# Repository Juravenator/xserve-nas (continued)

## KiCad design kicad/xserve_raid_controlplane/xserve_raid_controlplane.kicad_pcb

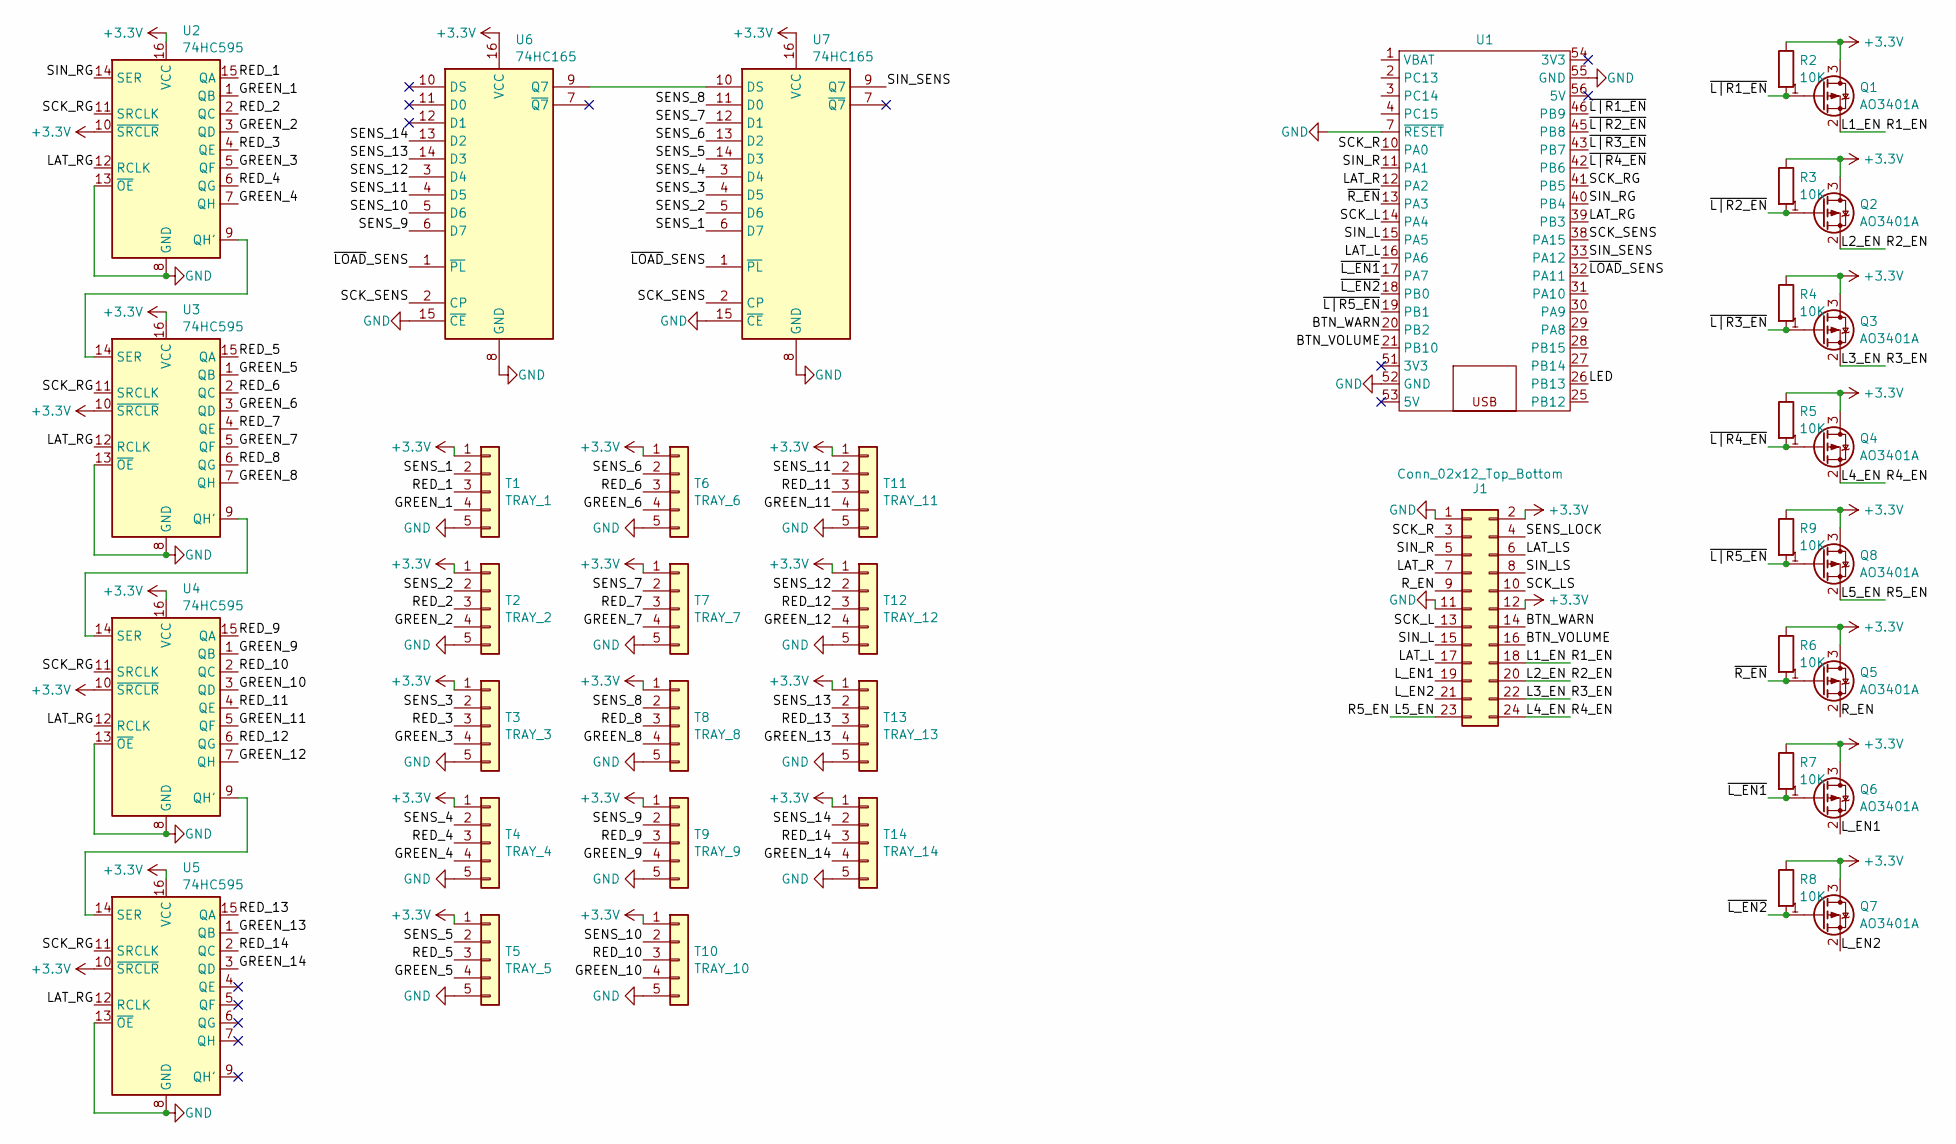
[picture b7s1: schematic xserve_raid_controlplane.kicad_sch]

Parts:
J1: Conn_02x12_Top_Bottom; PinHeader_2x12_P2.00mm_Vertical
Q1, Q2, Q3, Q4, Q5, Q6, Q7, Q8: AO3401A; SOT-23
R2, R3, R4, R5, R6, R7, R8, R9: 10K; R_Axial_DIN0204_L3.6mm_D1.6mm_P7.62mm_Horizontal
T1: TRAY_1; PinHeader_1x05_P2.54mm_Vertical
T2: TRAY_2; PinHeader_1x05_P2.54mm_Vertical
T3: TRAY_3; PinHeader_1x05_P2.54mm_Vertical
T4: TRAY_4; PinHeader_1x05_P2.54mm_Vertical
T5: TRAY_5; PinHeader_1x05_P2.54mm_Vertical
T6: TRAY_6; PinHeader_1x05_P2.54mm_Vertical
T7: TRAY_7; PinHeader_1x05_P2.54mm_Vertical
T8: TRAY_8; PinHeader_1x05_P2.54mm_Vertical
T9: TRAY_9; PinHeader_1x05_P2.54mm_Vertical
T10: TRAY_10; PinHeader_1x05_P2.54mm_Vertical
T11: TRAY_11; PinHeader_1x05_P2.54mm_Vertical
T12: TRAY_12; PinHeader_1x05_P2.54mm_Vertical
T13: TRAY_13; PinHeader_1x05_P2.54mm_Vertical
T14: TRAY_14; PinHeader_1x05_P2.54mm_Vertical
U1: blackpill
U2, U3, U4, U5: 74HC595; DIP-16_W7.62mm
U6, U7: 74HC165; DIP-16_W7.62mm

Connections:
+3.3V: J1.2, J1.12, Q1.3 (D), Q2.3 (D), Q3.3 (D), Q4.3 (D), Q5.3 (D), Q6.3 (D), Q7.3 (D), Q8.3 (D), R2.1, R3.1, R4.1, R5.1, R6.1, R7.1, R8.1, R9.1, T1.1, T2.1, T3.1, T4.1, T5.1, T6.1, T7.1, T8.1, T9.1, T10.1, T11.1, T12.1, T13.1, T14.1, U2.10 (~SRCLR), U2.16 (VCC), U3.10 (~SRCLR), U3.16 (VCC), U4.10 (~SRCLR), U4.16 (VCC), U5.10 (~SRCLR), U5.16 (VCC), U6.16 (VCC), U7.16 (VCC)
/BTN_VOLUME: J1.16, U1.21 (PB10)
/BTN_WARN: J1.14, U1.20 (PB2)
/GREEN_1: T1.4, U2.1 (QB)
/GREEN_2: T2.4, U2.3 (QD)
/GREEN_3: T3.4, U2.5 (QF)
/GREEN_4: T4.4, U2.7 (QH)
/GREEN_5: T5.4, U3.1 (QB)
/GREEN_6: T6.4, U3.3 (QD)
/GREEN_7: T7.4, U3.5 (QF)
/GREEN_8: T8.4, U3.7 (QH)
/GREEN_9: T9.4, U4.1 (QB)
/GREEN_10: T10.4, U4.3 (QD)
/GREEN_11: T11.4, U4.5 (QF)
/GREEN_12: T12.4, U4.7 (QH)
/GREEN_13: T13.4, U5.1 (QB)
/GREEN_14: T14.4, U5.3 (QD)
/L1_EN: J1.18, Q1.2 (S)
/L2_EN: J1.20, Q2.2 (S)
/L3_EN: J1.22, Q3.2 (S)
/L4_EN: J1.24, Q4.2 (S)
/L5_EN: J1.23, Q8.2 (S)
/LAT_L: J1.17, U1.16 (PA6)
/LAT_LS: J1.6
/LAT_R: J1.7, U1.12 (PA2)
/LAT_RG: U1.39 (PB3), U2.12 (RCLK), U3.12 (RCLK), U4.12 (RCLK), U5.12 (RCLK)
/LED: U1.26 (PB13)
/L_EN1: J1.19, Q6.2 (S)
/L_EN2: J1.21, Q7.2 (S)
/RED_1: T1.3, U2.15 (QA)
/RED_2: T2.3, U2.2 (QC)
/RED_3: T3.3, U2.4 (QE)
/RED_4: T4.3, U2.6 (QG)
/RED_5: T5.3, U3.15 (QA)
/RED_6: T6.3, U3.2 (QC)
/RED_7: T7.3, U3.4 (QE)
/RED_8: T8.3, U3.6 (QG)
/RED_9: T9.3, U4.15 (QA)
/RED_10: T10.3, U4.2 (QC)
/RED_11: T11.3, U4.4 (QE)
/RED_12: T12.3, U4.6 (QG)
/RED_13: T13.3, U5.15 (QA)
/RED_14: T14.3, U5.2 (QC)
/R_EN: J1.9, Q5.2 (S)
/SCK_L: J1.13, U1.14 (PA4)
/SCK_LS: J1.10
/SCK_R: J1.3, U1.10 (PA0)
/SCK_RG: U1.41 (PB5), U2.11 (SRCLK), U3.11 (SRCLK), U4.11 (SRCLK), U5.11 (SRCLK)
/SCK_SENS: U1.38 (PA15), U6.2 (CP), U7.2 (CP)
/SENS_1: T1.2, U7.6 (D7)
/SENS_2: T2.2, U7.5 (D6)
/SENS_3: T3.2, U7.4 (D5)
/SENS_4: T4.2, U7.3 (D4)
/SENS_5: T5.2, U7.14 (D3)
/SENS_6: T6.2, U7.13 (D2)
/SENS_7: T7.2, U7.12 (D1)
/SENS_8: T8.2, U7.11 (D0)
/SENS_9: T9.2, U6.6 (D7)
/SENS_10: T10.2, U6.5 (D6)
/SENS_11: T11.2, U6.4 (D5)
/SENS_12: T12.2, U6.3 (D4)
/SENS_13: T13.2, U6.14 (D3)
/SENS_14: T14.2, U6.13 (D2)
/SENS_LOCK: J1.4
/SIN_L: J1.15, U1.15 (PA5)
/SIN_LS: J1.8
/SIN_R: J1.5, U1.11 (PA1)
/SIN_RG: U1.40 (PB4), U2.14 (SER)
/SIN_SENS: U1.33 (PA12), U7.9 (Q7)
/~LOAD_SENS: U1.32 (PA11), U6.1 (~PL), U7.1 (~PL)
/~L_EN1: Q6.1 (G), R7.2, U1.17 (PA7)
/~L_EN2: Q7.1 (G), R8.2, U1.18 (PB0)
/~L|R1_EN: Q1.1 (G), R2.2, U1.46 (PB9)
/~L|R2_EN: Q2.1 (G), R3.2, U1.45 (PB8)
/~L|R3_EN: Q3.1 (G), R4.2, U1.43 (PB7)
/~L|R4_EN: Q4.1 (G), R5.2, U1.42 (PB6)
/~L|R5_EN: Q8.1 (G), R9.2, U1.19 (PB1)
/~R_EN: Q5.1 (G), R6.2, U1.13 (PA3)
GND: J1.1, J1.11, T1.5, T2.5, T3.5, T4.5, T5.5, T6.5, T7.5, T8.5, T9.5, T10.5, T11.5, T12.5, T13.5, T14.5, U1.7 (~RESET), U1.52 (GND), U1.55 (GND), U2.8 (GND), U2.13 (~OE), U3.8 (GND), U3.13 (~OE), U4.8 (GND), U4.13 (~OE), U5.8 (GND), U5.13 (~OE), U6.8 (GND), U6.15 (~CE), U7.8 (GND), U7.15 (~CE)
unnamed: U2.9 (QH'), U3.14 (SER)
unnamed: U3.9 (QH'), U4.14 (SER)
unnamed: U4.9 (QH'), U5.14 (SER)
unnamed: U6.9 (Q7), U7.10 (DS)

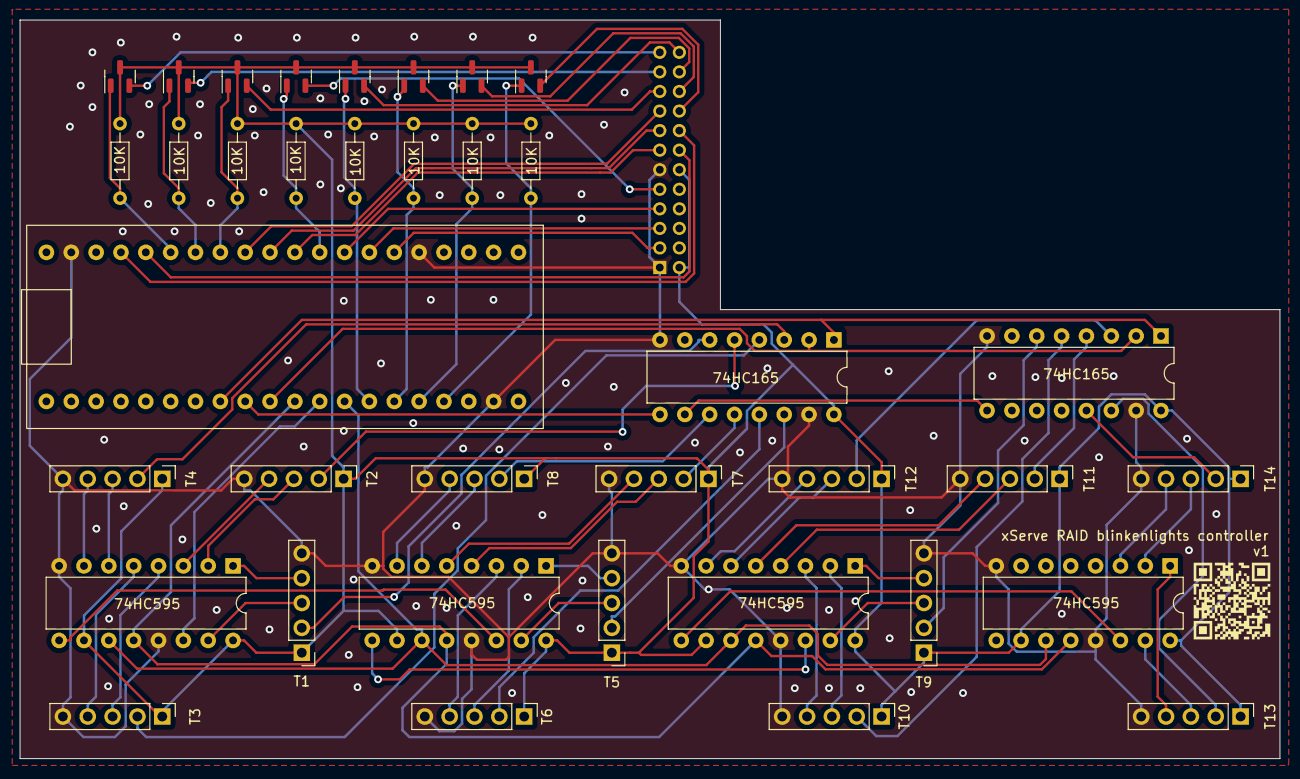
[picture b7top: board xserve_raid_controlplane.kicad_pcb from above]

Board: 2 copper layers, 128.8 x 75.5 mm, 39 parts (1 on the bottom side), 78 nets.

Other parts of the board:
v1: LOGO

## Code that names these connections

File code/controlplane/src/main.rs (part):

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    let led = Output::new(p.PC13, Level::High, Speed::Low);

    // // SATA status LED control
    // let sck_rg = Output::new(p.PA5, Level::Low, Speed::VeryHigh);
    // let sin_rg = Output::new(p.PA6, Level::Low, Speed::VeryHigh);
    // let lat_rg = Output::new(p.PA7, Level::Low, Speed::VeryHigh);

    // // SATA sensors
    // let sck_sens = Output::new(p.PA2, Level::Low, Speed::VeryHigh);
    // let sin_sens = Output::new(p.PA3, Level::Low, Speed::VeryHigh);
    // let nload_sens = Output::new(p.PA4, Level::Low, Speed::VeryHigh);

    // Center daughterboard LED control
    let sck = DMAShiftRegister::init_dma_pin(p.PB0);
    let driver_center = {
        let sin = p.PB1;
        let lat = p.PB2;
        let nen1 = p.PB3;
        let nen2 = p.PB4;
        let nen3 = p.PB5;
        let nen4 = p.PB6;
        let nen5 = p.PB7;
        LedDriver::<5, 2, 5>::new(
            sck,
            sin,
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
    // Left-side daughterboard LED control
    let driver_l = {
        let sin = p.PB8;
        let lat = p.PB10;
        let nen1 = p.PB9;
        let nen2 = p.PB12;
        LedDriver::<2, 1, 3>::new(sck, sin, lat, [nen1.degrade(), nen2.degrade()])
    };
    // Left-side daughterboard sensors
    let _btn_warn = Input::new(p.PA0, Pull::Down);
    let _btn_volume = Input::new(p.PA1, Pull::Down);

    // let btn_warn = ExtiInput::new(btn_warn, p.EXTI0);
    // let btn_volume = ExtiInput::new(btn_volume, p.EXTI1);
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        LedDriver::<1, 1, 4>::new(sck, sin, lat, [nen.degrade()])
    };
    // Right-side daughterboard sensors
    // let sens_lock = Input::new(p.PA10, Pull::Down);

    // // Hello world of GPIOB
    // pac::GPIOB.bsrr().write_value(Bsrr(0x0000FFFF));
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    interrupt::USART2.set_priority(Priority::P6);
    let spawner = EXECUTOR_BLINK.start(interrupt::USART2);
    spawner.spawn(run_blink(led)).unwrap();
    spawner.spawn(run_usb(p.USB_OTG_FS, p.PA12, p.PA11)).unwrap();

    let executor = EXECUTOR_LS.init(Executor::new());
    executor.run(|s| {
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}

#[embassy_executor::task]
async fn run_usb(fs: USB_OTG_FS, pa12: PA12, pa11: PA11) {
    // Create the driver, from the HAL.
    let mut ep_out_buffer = [0u8; 256];
    let mut config = embassy_stm32::usb_otg::Config::default();
    config.vbus_detection = false;
    let driver = Driver::new_fs(fs, Irqs, pa12, pa11, &mut ep_out_buffer, config);

    // Create embassy-usb Config
    let mut config = embassy_usb::Config::new(0xc0de, 0xcafe);
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
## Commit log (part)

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2023-12-11 initial dump
2023-12-17 TIM1 DMA to GPIOB works
2023-12-18 21Mhz test clock
2023-12-18 TIM1 steers multiple DMAs
2023-12-24 drivers and pulses, rainbow demo
2024-02-08 new board, unit tests, formatting, more efficient DMA calc
2024-02-09 USB works again
2024-02-09 embassy update
2026-03-19 starter nixos setup
2026-03-19 whoami service for tests
2026-03-19 try to always redirect to https
2026-03-19 enable letsencrypt
2026-03-19 whoami on https
2026-03-19 move apps to folders
2026-03-19 plex
2026-03-19 traefik has persistent data for cert cache
2026-03-19 google login in argocd sucks ass
2026-03-20 add starter samba config
2026-03-20 less tedious names for plex workloads
2026-03-20 ddns updater
2026-03-20 owncloud
2026-03-20 internal-only doesn't work
2026-03-20 transmission
2026-03-20 ensure google login is only for me
2026-03-20 more samba shares
2026-03-20 xanen has samba
2026-03-20 disks go zzz
2026-03-22 actually enable samba
2026-03-22 sanoid config file
2026-03-22 preserve source ips so internal-only can work again
2026-03-22 test internal-only on whoami
2026-03-22 Revert "internal-only doesn't work"
    This reverts commit 27876e44d5a54cd8386929bd644201b59b7d6e17.
2026-03-22 internal only must not mess with intra-service traffic
2026-03-23 dashboard
2026-03-23 uptick dashboard
2026-03-30 refine sanoid & syncoid
2026-03-30 fluufff stuff
2026-03-30 enable samba network discovery
2026-03-30 update dashboard
2026-04-02 periodic zpool scrubbing
2026-04-02 zfs snapshot & replication refinements
2026-04-02 dashboard update
2026-04-02 woofdisk share
2026-04-05 oops
2026-04-22 add unifi deployment
2026-04-22 uptick unifi
2026-04-22 unifi AP restart job
2026-04-22 adjust unifi deployments
2026-05-09 switch to protonvpn
2026-06-01 upgrade traefik
2026-06-01 update transmission
